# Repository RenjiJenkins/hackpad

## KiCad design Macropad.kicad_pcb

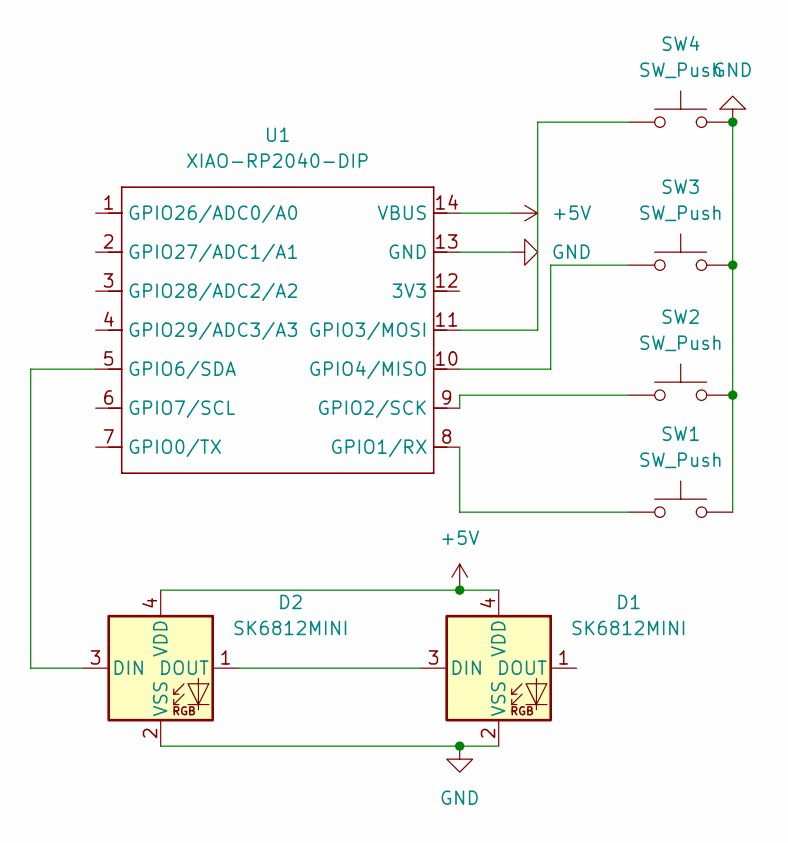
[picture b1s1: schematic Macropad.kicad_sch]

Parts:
D1, D2: SK6812MINI; LED_SK6812MINI_PLCC4_3.5x3.5mm_P1.75mm
SW1, SW2, SW3, SW4: SW_Push; SW_Cherry_MX_1.00u_PCB
U1: XIAO-RP2040-DIP

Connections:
+5V: D1.4 (VDD), D2.4 (VDD), U1.14 (VBUS)
GND: D1.2 (VSS), D2.2 (VSS), SW1.2, SW2.2, SW3.2, SW4.2, U1.13 (GND)
unnamed: D1.3 (DIN), D2.1 (DOUT)
unnamed: D2.3 (DIN), U1.5 (GPIO6/SDA)
unnamed: SW1.1, U1.8 (GPIO1/RX)
unnamed: SW2.1, U1.9 (GPIO2/SCK)
unnamed: SW4.1, U1.11 (GPIO3/MOSI)
unnamed: SW3.1, U1.10 (GPIO4/MISO)

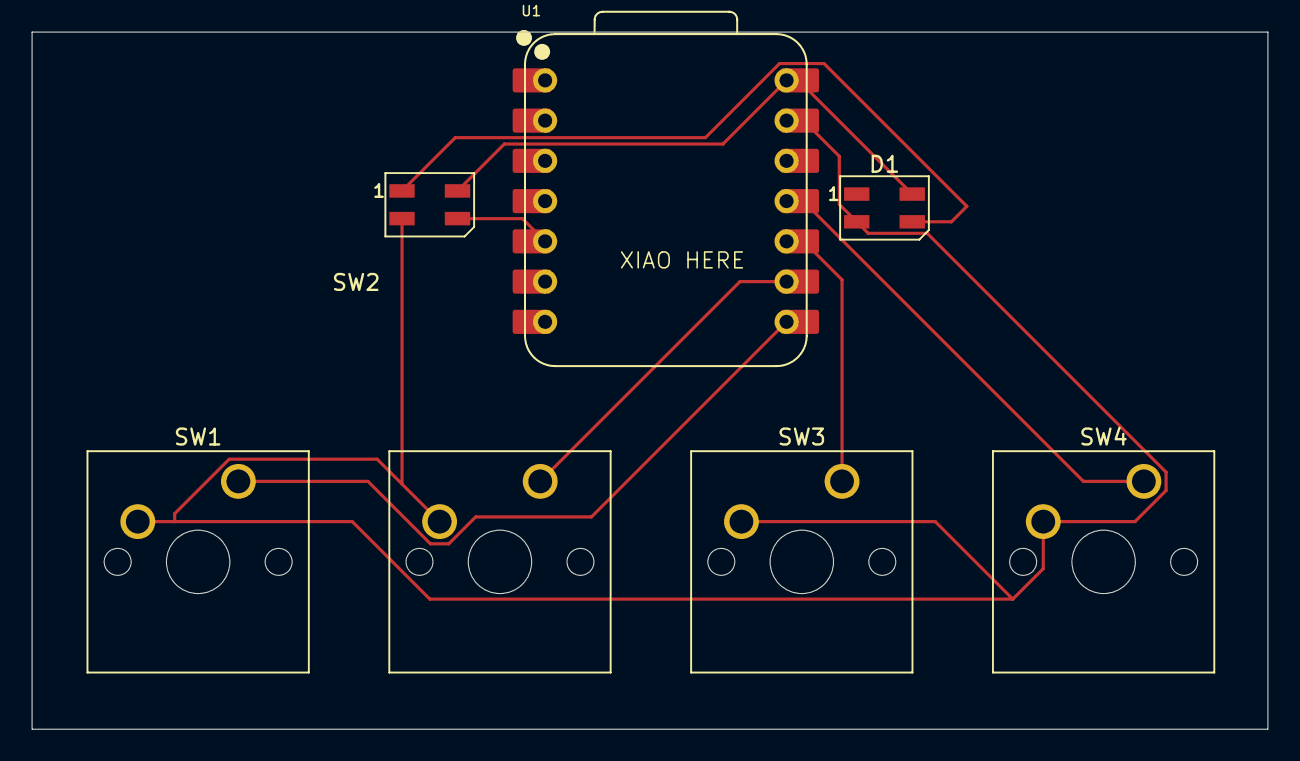
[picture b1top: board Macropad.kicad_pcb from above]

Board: 2 copper layers, 78.0 x 44.0 mm, 7 parts (0 on the bottom side), 8 nets.

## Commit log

2026-01-02 Full Hackpad STEP CAD file
2026-01-02 KiCAD Files
